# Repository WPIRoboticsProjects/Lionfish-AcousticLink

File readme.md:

This is the repo for acoustic modem and localization from acoustic modem

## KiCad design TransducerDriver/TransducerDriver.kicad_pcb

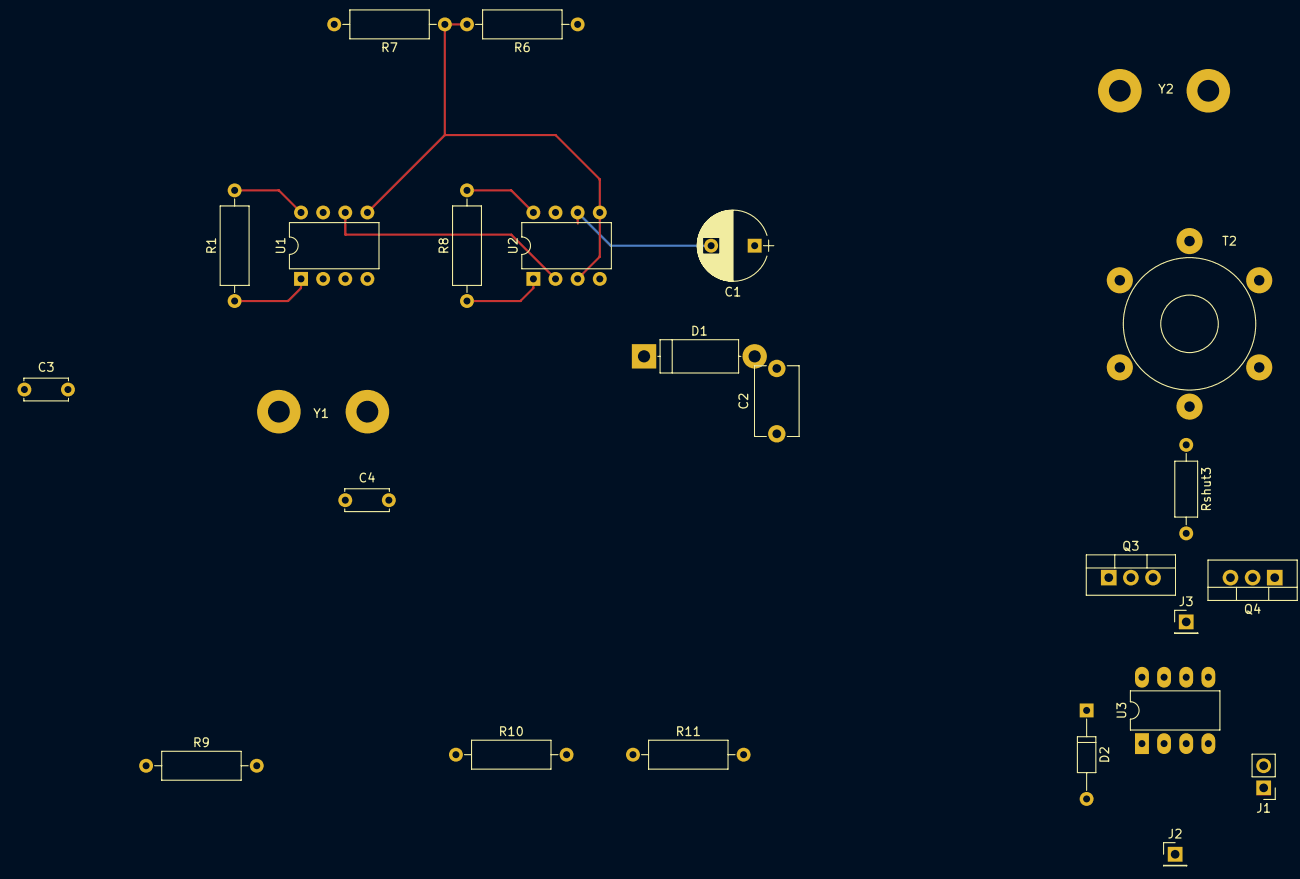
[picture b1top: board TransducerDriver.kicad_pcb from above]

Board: 2 copper layers, 25 parts (0 on the bottom side), 26 nets.

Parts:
C1: 159nF; CP_Radial_D8.0mm_P5.00mm
C2: 10nF; C_Disc_D8.0mm_W5.0mm_P7.50mm
C3, C4: 0.1u; C_Disc_D5.0mm_W2.5mm_P5.00mm
D1: 1N4148; D_5W_P12.70mm_Horizontal
D2: 1N4007; D_DO-35_SOD27_P10.16mm_Horizontal
J1: ModSigJack; Pin_Header_Straight_1x02_Pitch2.54mm
J2, J3: BattJack; Pin_Header_Straight_1x01_Pitch2.54mm
Q3, Q4: IRF540N; TO-220-3_Vertical
R1, R8: 101; R_Axial_DIN0309_L9.0mm_D3.2mm_P12.70mm_Horizontal
R6, R7: 4K; R_Axial_DIN0309_L9.0mm_D3.2mm_P12.70mm_Horizontal
R9: 530; R_Axial_DIN0309_L9.0mm_D3.2mm_P12.70mm_Horizontal
R10: 2Khom; R_Axial_DIN0309_L9.0mm_D3.2mm_P12.70mm_Horizontal
R11: 1Kohm; R_Axial_DIN0309_L9.0mm_D3.2mm_P12.70mm_Horizontal
Rshut3: 0.01; R_Axial_DIN0207_L6.3mm_D2.5mm_P10.16mm_Horizontal
T2: Transformer_SP_1S 1:10; Transformer_Toroid_Tapped_Horizontal_D14.0mm_Amidon-T50
U1, U2: INA217; DIP-8_W7.62mm
U3: TC427; DIP-8_W7.62mm_LongPads
Y1, Y2: Crystal; WireConnection_2.50mmDrill

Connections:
+BATT: D2.2, J2.1, R6.1, Rshut3.2, U1.7, U2.7
/MicroInput: R10.2, R11.1
/Vref: R6.2, R7.1, U1.5, U2.3, U2.5
GND: C2.1, J3.1, Q3.3, Q4.3, R7.2, R9.2, R11.2, U1.4, U2.4, U3.3
ModSig+: J1.1, U3.2
ModSig-: J1.2, U3.4
unnamed: C1.1, D1.1
unnamed: C1.2, U2.6
unnamed: C2.2, D1.2, R9.1, R10.1
unnamed: C3.1, U1.2
unnamed: C3.2, Y1.1
unnamed: C4.1, U1.3
unnamed: C4.2, Y1.2
unnamed: D2.1, U3.6
unnamed: Q3.1, U3.7
unnamed: Q3.2, T2.1
unnamed: Q4.1, U3.5
unnamed: Q4.2, T2.3
unnamed: R1.1, U1.1
unnamed: R1.2, U1.8
unnamed: R8.1, U2.1
unnamed: R8.2, U2.8
unnamed: Rshut3.1, T2.2
unnamed: T2.4, Y2.2
unnamed: T2.5, Y2.1
unnamed: U1.6, U2.2

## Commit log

2019-10-28 added initial readme
2019-10-28 init
    init
2019-10-29 Made waveform gen for any sample rate and base frequency
2019-10-29 included .gitignore file
2019-10-31 demodulate work in progress
2019-11-07 created Matlab calculation for transmission loss, and attached figure for result from different method
2019-11-07 added design for switching battery
2019-11-07 added ESD zener for MOSFET design
2019-11-07 Revert "Merge branch 'master' of https://github.com/LionfishMQP/AcousticLink"
    This reverts commit a923de0f6f5281807e581be3a9d295d99ad474c0, reversing
    changes made to ccfcc6052f2c2148d2317a675659a02fa5cdc53d.
2019-11-07 Revert "Revert "Merge branch 'master' of https://github.com/LionfishMQP/AcousticLink""
    This reverts commit bcc0f9a52feea505232c62d8da3853226641cb11.
2019-11-12 added design for distributed power cycle
2019-11-19 ook c files
2019-11-21 ook files renamed to encode binary
2019-11-25 might work now
2019-11-30 remove auto save
2019-11-30 created basic decoding file, and added csv write to matlab
2019-12-03 OOK Modulation + Cleanup
    Added modulation + writing to csv in encode.c
    Organized python and c file folders
2019-12-04 finished ook modulation to csv
2019-12-04 encode fix
2019-12-04 Making matlab signal visulazation
2019-12-04 new SAMPLE_RATE
2019-12-05 added fft functions
2019-12-05 encode changes
2019-12-05 changed decode file read limit
2019-12-05 changed filter range
2019-12-09 fixes + settings (WIP)
2020-02-03 PWM driver on arm board, transducer circuit
2020-02-04 fifo implement + some old code
    Added fifo for tx messages
    copied in old functions from previous C files (Encode.c / Decode.c)
2020-02-10 changes
    sampling adc + buttons
2020-02-15 updates
    compiles for me now, added support for buttons and sampling .c
2020-02-15 studies on transducer
2020-02-16 small change on InsAmp. Input pull to vref
2020-02-18 more updates
    processing buffer and tx_message
2020-02-18 rough structure for processing ADC RX
2020-02-19 more impedance data
2020-02-19 impedance calculation done
2020-02-23 more calculation
2020-02-24 added timer files
2020-02-25 trying to add timer1, but get system fault
2020-02-25 CRC + DMA clean up
    Changes for CRC, and DMA clean up
2020-02-25 crc changes
2020-02-26 impedance matching work done
2020-02-26 merge
2020-02-26 structs for ID/COMMAND codes + clean up
2020-02-28 construct packet + process_request
2020-02-28 todo list for help
    need help with PWM and Ethernet ISR setup
2020-02-28 more work
2020-02-29 more mod on circuits
2020-03-02 more measurement and update schematic
2020-03-02 Ethernet + Timer Fix
2020-03-02 more measurement and schmatic update
2020-03-03 reorganizing changes + Ethernet + Protocol.c
    most new code is written with STATIC variables to keep names in-tact
2020-03-03 small changes
2020-03-03 project setting
2020-03-03 timer interrupt working now. but setting pins twice as fast. it shouldn't
2020-03-03 timer interrupt removed double trigger
2020-03-03 reorganization
    fully builds. need to test two way communication + write sending message methods.
    Ethernet as a stretch
2020-03-03 timer1 work, and is read to trigger ADC as well
2020-03-03 transmit works now. It will clock the PWM out according to data it get
2020-03-03 changed ADC (no DMA)
2020-03-03 slight changes
2020-03-03 always trasmiting fake data now
2020-03-04 small changes
    construct packet was failing because of weird int type issues
2020-03-04 CRC redo + sampling changes
2020-03-04 CRC implementation + adjustment for TX
2020-03-04 change bit parsing to section style
2020-03-25 sampling problems
    Will sample up to 9 or so bits into raw_rx but will not read whole packet. problem with bit xor or read_for
2020-03-26 duplicate read_for with edge triggering
2020-04-08 edge trigger changes
2020-04-08 crc update
2020-04-08 sampling Works!!!
2020-04-15 rx / tx full merge
    test1
2020-04-15 cleanup
2020-04-15 more merge changes
2020-04-21 Revert "more merge changes"
    This reverts commit 9ff77436987e17026d60a138173b1d5c7bb23e4e.
2020-04-21 Revert "cleanup"
    This reverts commit cc72b08c53214a4f9a6eb29a68c55144737209b3.
2020-04-21 Revert "rx / tx full merge"
    This reverts commit 94f6001b4b1806fa120cbfeac09636d83672bcb4.
2020-05-18 final clean up
